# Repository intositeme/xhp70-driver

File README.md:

# LED Driver Rev 2b

### AL8871Q IC buck mode driver with ATTiny85 mcu for pwm. NTC Thermistor connected to Attiny85 to control pwm.

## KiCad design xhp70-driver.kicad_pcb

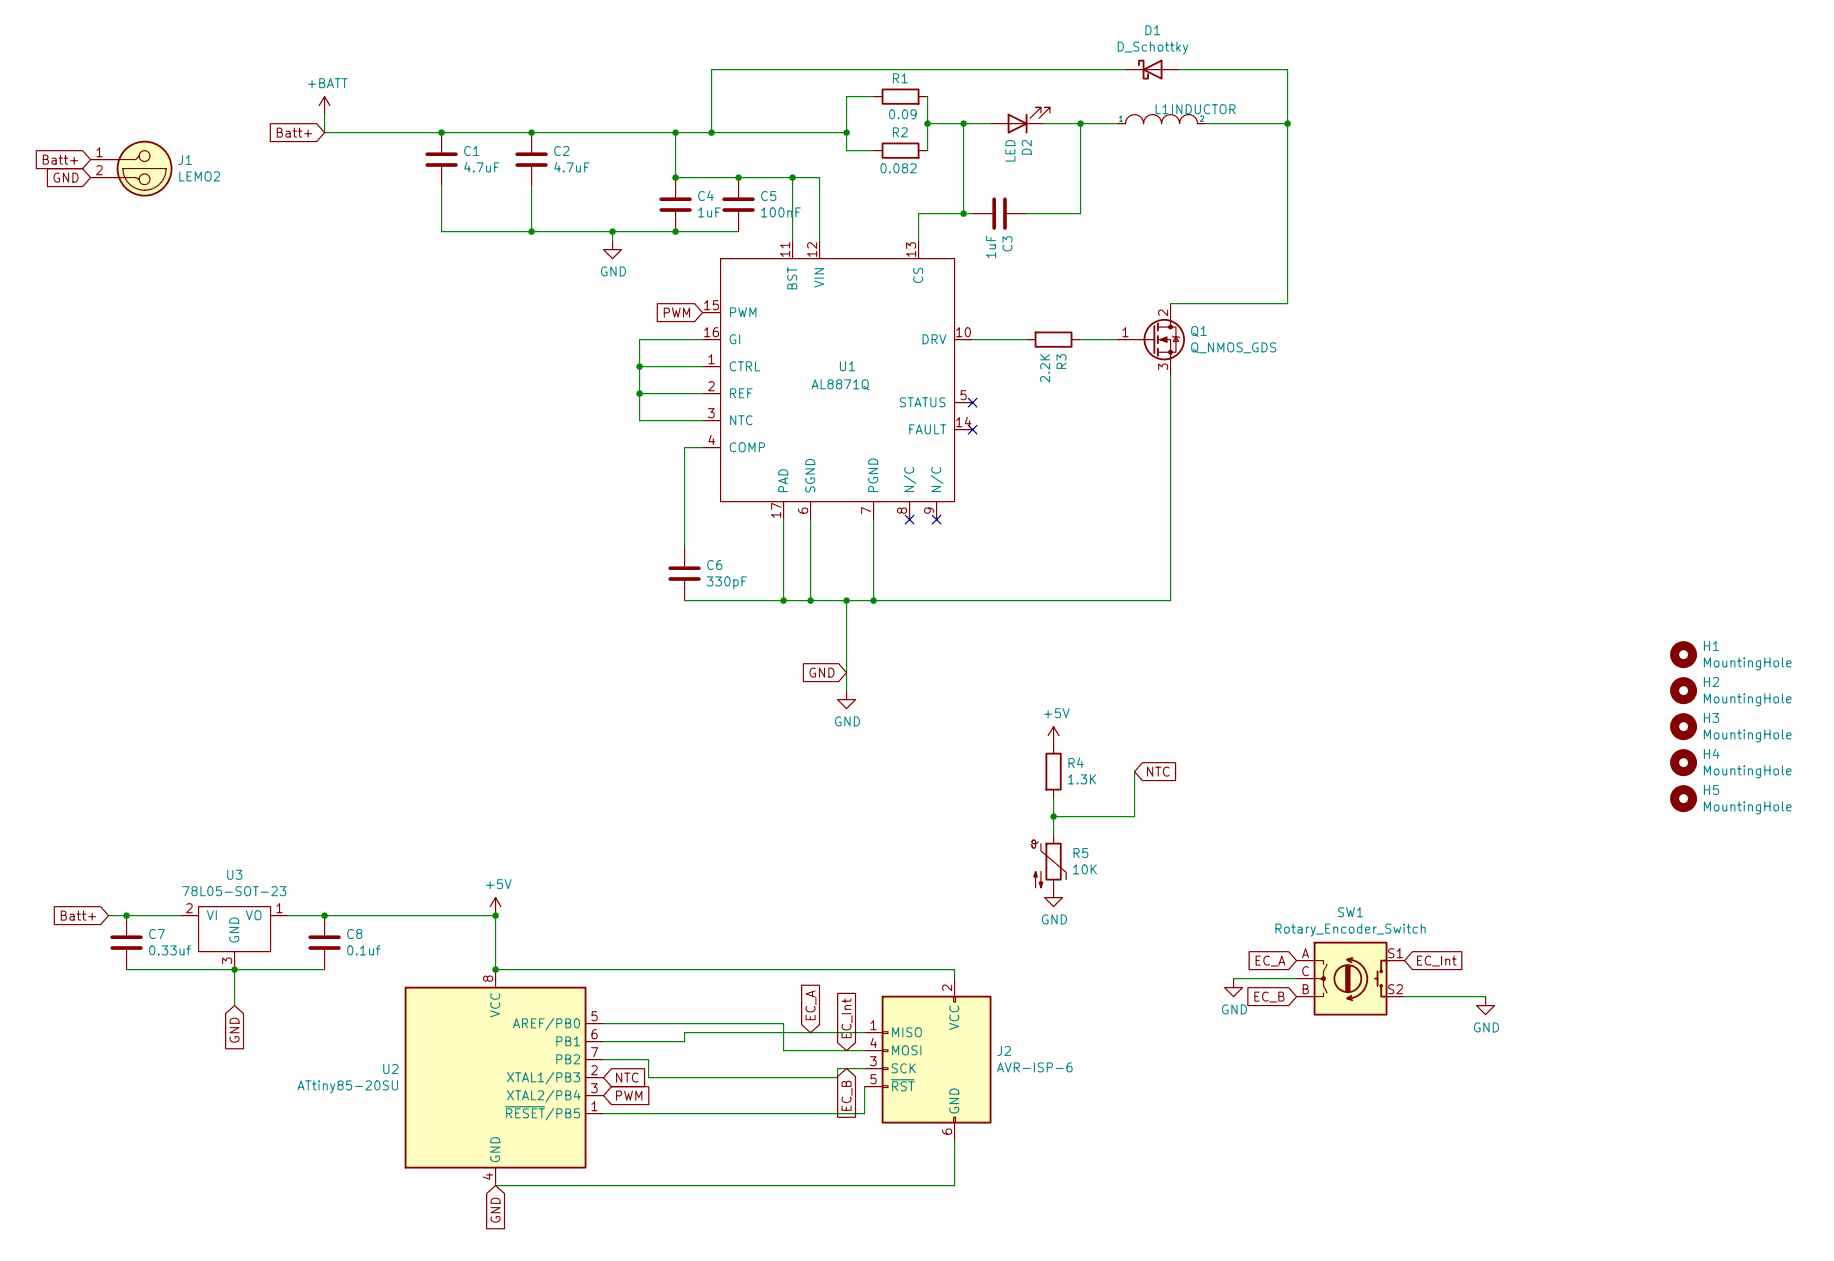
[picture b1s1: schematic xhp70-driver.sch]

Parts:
C1, C2: 4.7uF; C_1206_3216Metric_Pad1.33x1.80mm_HandSolder
C3, C4: 1uF; C_1206_3216Metric_Pad1.33x1.80mm_HandSolder
C5: 100nF; C_0805_2012Metric
C6: 330pF; C_0805_2012Metric
C7: 0.33uf; C_0805_2012Metric
C8: 0.1uf; C_0805_2012Metric
D1: D_Schottky; TO-220-2_Horizontal_TabUp-no-mounting-hole
D2: LED; TestPoint_2Pad_4.0x4.0mm
H1, H2, H3, H4, H5: MountingHole; MountingHole_2.2mm_M2_ISO7380_Pad
J1: LEMO2; TestPoint_2Pad_4.0x4.0mm
J2: AVR-ISP-6; JST_SH_BM06B-SRSS-TB_1x06-1MP_P1.00mm_Vertical
L1: INDUCTOR; L_12x12mm_H8mm
Q1: Q_NMOS_GDS; TO-220-3_Horizontal_TabUp-no-mounting-hole
R1: 0.09; R_2512_6332Metric
R2: 0.082; R_2512_6332Metric
R3: 2.2K; R_0805_2012Metric
R4: 1.3K; R_0805_2012Metric
R5: 10K; JST_SH_BM02B-SRSS-TB_1x02-1MP_P1.00mm_Vertical
SW1: Rotary_Encoder_Switch
U1: AL8871Q
U2: ATtiny85-20SU; SOIJ-8_5.3x5.3mm_P1.27mm
U3: 78L05-SOT-23; SOT-23

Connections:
+5V: C8.1, J2.2 (VCC), R4.1, U2.8 (VCC), U3.1 (VO)
Batt+: C1.1, C2.1, C4.1, C5.1, C7.1, D1.1 (K), J1.1, R1.1, R2.1, U1.11 (BST), U1.12 (VIN), U3.2 (VI)
EC_A: J2.1 (MISO), SW1.A, U2.6 (PB1)
EC_B: J2.3 (SCK), SW1.B, U2.7 (PB2)
EC_Int: J2.4 (MOSI), SW1.S1, U2.5 (AREF/PB0)
GND: C1.2, C2.2, C4.2, C5.2, C6.2, C7.2, C8.2, J1.2, J2.6 (GND), Q1.3 (S), R5.2, SW1.C, SW1.S2, U1.6 (SGND), U1.7 (PGND), U1.17 (PAD), U2.4 (GND), U3.3 (GND)
NTC: R4.2, R5.1, U2.2 (XTAL1/PB3)
unnamed: C3.1, D2.1 (K), L1.1
unnamed: C3.2, D2.2 (A), R1.2, R2.2, U1.13 (CS)
unnamed: C6.1, U1.4 (COMP)
unnamed: D1.2 (A), L1.2, Q1.2 (D)
unnamed: J2.5 (~RST), U2.1 (~RESET~/PB5)
unnamed: Q1.1 (G), R3.1
unnamed: R3.2, U1.10 (DRV)
unnamed: U1.1 (CTRL), U1.2 (REF), U1.3 (NTC), U1.16 (GI)
PWM: U1.15 (PWM), U2.3 (XTAL2/PB4)

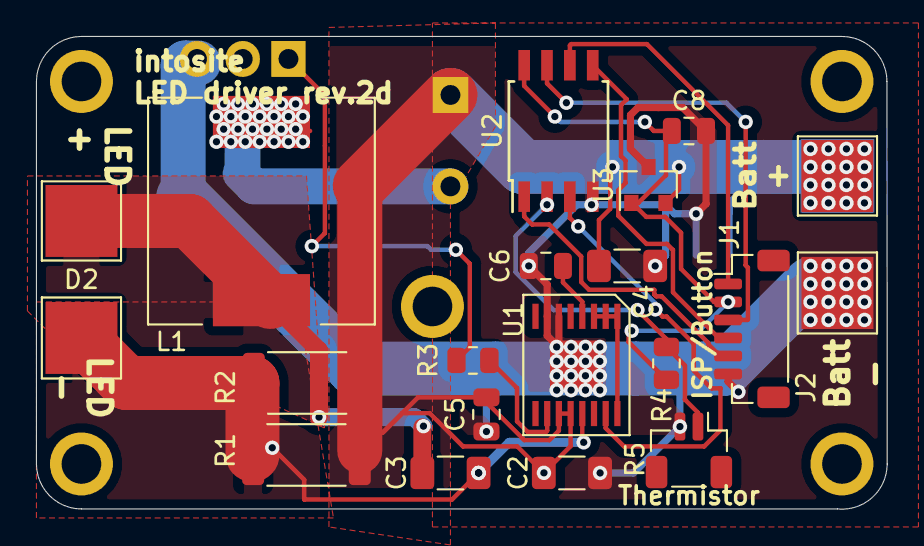
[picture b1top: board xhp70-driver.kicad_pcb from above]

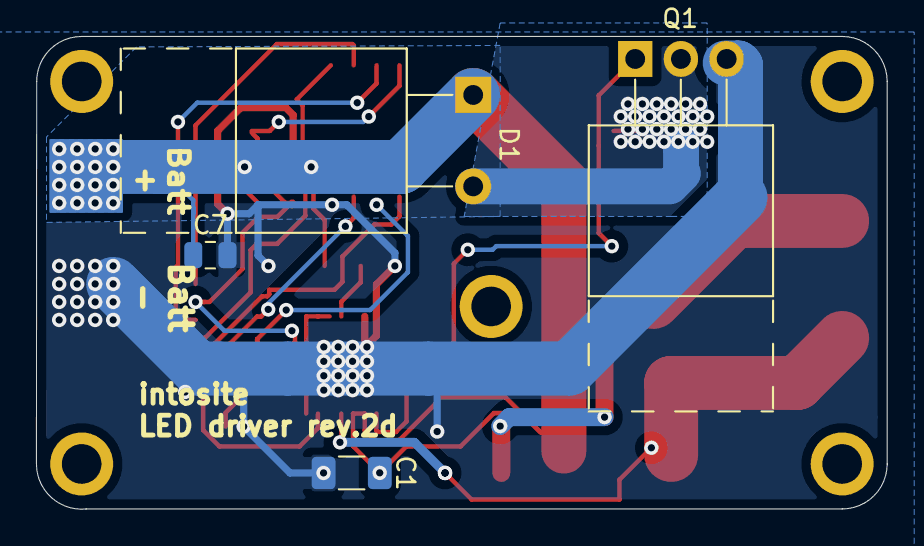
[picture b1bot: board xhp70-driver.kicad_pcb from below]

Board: 2 copper layers, 47.3 x 26.3 mm, 27 parts (4 on the bottom side), 16 nets.

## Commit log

2021-02-17 Initial files
2021-02-17 Layout schematic, created AL8871Q symbol and footprint. Layout PCB.
    Pending values for components and PCB traces.
2021-02-26 Added Attiny85 MCU to control PWM of AL8871Q
2021-02-27 Added components and route connections in xhp70-driver-test-route.pro file
2021-02-27 Reposition and changed connector. Reroute traces
2021-02-27 Tweak zone fills
2021-02-27 Added name
2021-02-27 fixed unconnected tracks
2021-03-04 Added thermal analysis report
2021-03-06 LED driver rev.1b - Added decoupling Capacitors for Attiny
2021-03-07 Rev 2a - route NTC Thermistor to Attiny to control output
2021-03-08 Added new thermal analysis
2021-03-16 L7805 schematic pinout is wrong. Needs reroute. `
2021-03-16 Updated routing and added thicker traces
2021-03-17 Redo. Same as rev.2b
2021-03-17 Added gitignore
2021-03-17 Remove fp-info-cache
2021-04-12 Added interactive bom
2021-04-21 Changed LDO to 78L05 linear voltage regulator
2021-04-21 Revised sense resistor placement
